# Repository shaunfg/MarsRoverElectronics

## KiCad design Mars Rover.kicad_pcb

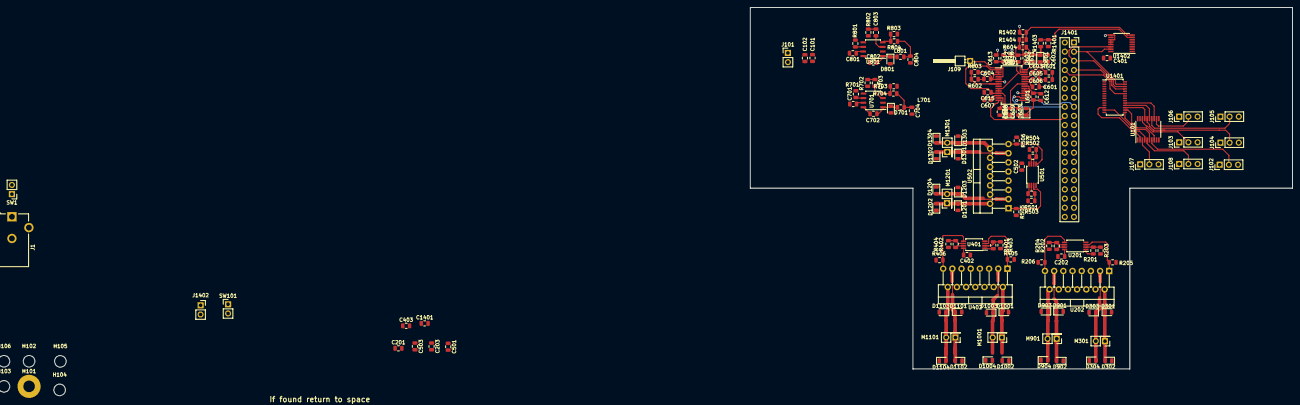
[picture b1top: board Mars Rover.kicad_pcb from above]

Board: 2 copper layers, 150.0 x 100.0 mm, 141 parts (0 on the bottom side), 101 nets.

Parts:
C101, C614, C616: 22uF; C_0805_2012Metric
C102, C601, C602, C605, C606, C610, C611, C612: 0.1uF; C_0805_2012Metric
C201, C202, C203, C401, C402, C403, C501, C502, C503: 100nF; C_0805_2012Metric
C603, C607, C608: 1nF; C_0805_2012Metric
C604: 1uF; C_0805_2012Metric
C609, C701, C702, C801, C802, C1401: C; C_0805_2012Metric
C613: 0.22uF; C_0805_2012Metric
C615: 4.7uF; C_0805_2012Metric
C703, C704, C803, C804: 220pF; C_0805_2012Metric
D301, D302, D303, D304, D601, D604, D901, D902, D903, D904, D1001, D1002, D1003, D1004, D1101, D1102, D1103, D1104, D1201, D1202, D1203, D1204, D1301, D1302, D1303, D1304: DIODE; D_0805_2012Metric
D602, D603, D701, D801: D_Schottky; D_0805_2012Metric
H101: MountingHole_Pad; MountingHole_3.2mm_M3_Pad
H102, H103, H104, H105, H106: MountingHole; MountingHole_3.2mm_M3
J1: Barrel_Jack; BarrelJack_CUI_PJ-102AH_Horizontal
J101: Conn_01x02; PinHeader_1x02_P2.54mm_Vertical
J102, J103, J104, J105, J106, J107, J108: Conn_01x03; PinHeader_1x03_P2.54mm_Vertical
J109: Conn_01x01; PinHeader_1x01_P2.54mm_Horizontal
J1401: Raspberry_Pi_2_3; PinSocket_2x20_P2.54mm_Vertical
J1402: Conn_01x02; PinSocket_1x02_P2.54mm_Vertical
L601: INDUCTOR; L_0805_2012Metric
L701, L801: L; L_0805_2012Metric
M301, M901, M1001, M1101, M1201, M1301: Motor_DC; PinHeader_2x01_P2.54mm_Vertical
R201, R202, R401, R402, R501, R502: 1k; R_0805_2012Metric
R203, R204, R403, R404, R503, R504, R601, R703, R803: 10k; R_0805_2012Metric
R205, R206, R405, R406, R505, R506: 200mR; R_0805_2012Metric
R602, R603, R1401, R1402, R1403, R1404: R; R_0805_2012Metric
R604: 0.05R; R_0805_2012Metric
R701, R801: 200k; R_0805_2012Metric
R702, R802: 68k; R_0805_2012Metric
R704: 51k; R_0805_2012Metric
R804: 75k; R_0805_2012Metric
SW1: KILLSWITCH; PinHeader_1x02_P2.54mm_Vertical
SW101: CHARGING; PinHeader_1x02_P2.54mm_Vertical
U101: 74HCT244; TSSOP-20_4.4x6.5mm_P0.65mm
U201, U401, U501: OP279; TSSOP-8_4.4x3mm_P0.65mm
U202, U402, U502: L298HN; TO-220-15_P2.54x2.54mm_StaggerOdd_Lead4.58mm_Vertical
U601: MAX1758; SSOP-28_5.3x10.2mm_P0.65mm
U701, U801: MP2467; SOIC-8_3.9x4.9mm_P1.27mm
U1401: PCA9685PW; TSSOP-28_4.4x9.7mm_P0.65mm
U1402: ADS7828; TSSOP-16_4.4x5mm_P0.65mm

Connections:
+3V3: J1401.1, J1401.17
+5V: C201.2, C202.1, C401.2, C402.1, C501.2, C502.1, C704.1, C1401.1, J1401.2, J1401.4, J1402.1, L701.2, R704.2, U201.8, U202.6, U202.9, U202.11, U401.8, U402.6, U402.9, U402.11, U501.8, U502.6, U502.9, U502.11, U1401.28, U1402.16
+7.5V: C804.1, J102.3, J103.3, J104.3, J105.3, J106.3, J107.3, J108.3, L801.2, R804.2, U101.20
+12V: C203.2, C403.2, C503.2, C801.1, D301.2, D303.2, D901.2, D903.2, D1001.2, D1003.2, D1101.2, D1103.2, D1201.2, D1203.2, D1301.2, D1303.2, SW101.2, U202.4, U402.4, U502.4, U801.7
/Battery Connection and Charge Management/BATT: C101.1, C102.2, J101.2, U601.8
/Battery Connection and Charge Management/CHRG_VL: C615.1, D604.1, U601.1, U601.11
/Battery Connection and Charge Management/THERM: J109.1, U601.4
/Battery Connection and Charge Management/~FASTCHRG: J1401.15, U601.15
/Battery Connection and Charge Management/~FAULT: J1401.18, U601.14
/Battery Connection and Charge Management/~FULLCHRG: J1401.16, U601.16
/Digital logic/HK0: R201.1, U201.1, U1402.1
/Digital logic/HK1: R202.1, U201.7, U1402.2
/Digital logic/HK2: R401.1, U401.1, U1402.3
/Digital logic/HK3: R402.1, U401.7, U1402.4
/Digital logic/HK4: R501.1, U501.1, U1402.5
/Digital logic/HK5: R502.1, U501.7, U1402.6
/Digital logic/POL0: J1401.35, U202.7
/Digital logic/POL1: J1401.38, U202.12
/Digital logic/POL2: J1401.40, U402.7
/Digital logic/POL3: J1401.36, U402.12
/Digital logic/POL4: J1401.27, U502.7
/Digital logic/POL5: J1401.28, U502.12
/Digital logic/PWM0: U202.5, U1401.6
/Digital logic/PWM1: U202.10, U1401.7
/Digital logic/PWM2: U402.5, U1401.8
/Digital logic/PWM3: U402.10, U1401.9
/Digital logic/PWM4: U502.5, U1401.10
/Digital logic/PWM5: U502.10, U1401.11
/Digital logic/PWM6: U101.2, U1401.12
/Digital logic/PWM7: U101.4, U1401.13
/Digital logic/PWM8: U101.6, U1401.15
/Digital logic/PWM9: U101.8, U1401.16
/Digital logic/PWMA: U101.17, U1401.17
/Digital logic/PWMB: U101.15, U1401.18
/Digital logic/PWMC: U101.13, U1401.19
/Digital logic/SCL: J1401.5, U1401.26, U1402.14
/Digital logic/SDA: J1401.3, U1401.27, U1402.15
/Digital logic/~OE: J1401.8, U1401.23
/Motor/V1: D301.1, D302.2, M301.1, U202.2
/Motor/V2: D303.1, D304.2, M301.2, U202.3
/VIN_RAW: D601.1, D602.2, R1403.1, SW1.2
/VMOTOR: C610.2, C613.1, C614.1, C616.1, C701.1, R604.2, R1404.2, SW101.1, U601.9, U601.10, U601.26, U701.7
/sheet5C45D717/V1: D901.1, D902.2, M901.1, U202.13
/sheet5C45D717/V2: D903.1, D904.2, M901.2, U202.14
/sheet5C45DA5C/V1: D1001.1, D1002.2, M1001.1, U402.2
/sheet5C45DA5C/V2: D1003.1, D1004.2, M1001.2, U402.3
/sheet5C45DEF9/V1: D1101.1, D1102.2, M1101.1, U402.13
/sheet5C45DEF9/V2: D1103.1, D1104.2, M1101.2, U402.14
/sheet5C45F77A/V1: D1201.1, D1202.2, M1201.1, U502.2
/sheet5C45F77A/V2: D1203.1, D1204.2, M1201.2, U502.3
/sheet5C45FA3C/V1: D1301.1, D1302.2, M1301.1, U502.13
/sheet5C45FA3C/V2: D1303.1, D1304.2, M1301.2, U502.14
GND: C101.2, C102.1, C201.1, C202.2, C203.1, C401.1, C402.2, C403.1, C501.1, C502.2, C503.1, C601.2, C602.1, C603.2, C604.1, C605.2, C606.2, C607.2, C608.2, C610.1, C611.1, C612.2, C613.2, C614.2, C615.2, C616.2, C701.2, C704.2, C801.2, C804.2, C1401.2, D302.1, D304.1, D603.2, D701.2, D801.2, D902.1, D904.1, D1002.1, D1004.1, D1102.1, D1104.1, D1202.1, D1204.1, D1302.1, D1304.1, H101.1, J1.2, J101.1, J102.1, J103.1, J104.1, J105.1, J106.1, J107.1, J108.1, J1401.6, J1401.9, J1401.14, J1401.20, J1401.25, J1401.30, J1401.34, J1401.39, J1402.2, R203.2, R204.2, R205.2, R206.2, R403.2, R404.2, R405.2, R406.2, R503.2, R504.2, R505.2, R506.2, R602.2, R701.1, R702.2, R703.1, R801.1, R802.2, R803.1, R1401.2, R1402.2, U101.1, U101.10, U101.19, U201.4, U202.8, U401.4, U402.8, U501.4, U502.8, U601.6, U601.18, U701.5, U801.5, U1401.1, U1401.2, U1401.3, U1401.4, U1401.5, U1401.14, U1401.24, U1402.9, U1402.11, U1402.12, U1402.13
unnamed: C601.1, R601.2
unnamed: C602.2, D601.2, U601.28
unnamed: C603.1, R601.1, U601.25
unnamed: C604.2, R603.2, U601.2, U601.3, U601.5
unnamed: C605.1, U601.24
unnamed: C606.1, U601.23
unnamed: C607.1, U601.12
unnamed: C608.1, U601.13
unnamed: C609.1, D603.1, L601.1, U601.19, U601.20
unnamed: C609.2, D604.2, U601.22
unnamed: C611.2, D602.1, R604.1, U601.27
unnamed: C612.1, L601.2, U601.21
unnamed: C702.1, U701.8
unnamed: C702.2, D701.1, L701.1, U701.1
unnamed: C703.1, U701.3
unnamed: C703.2, R702.1
unnamed: C802.1, U801.8
unnamed: C802.2, D801.1, L801.1, U801.1
unnamed: C803.1, U801.3
unnamed: C803.2, R802.1
unnamed: J1.1, SW1.1
unnamed: J102.2, U101.7
unnamed: J103.2, U101.18
unnamed: J104.2, U101.16
unnamed: J105.2, U101.14
unnamed: J106.2, U101.12
unnamed: J107.2, U101.3
unnamed: J108.2, U101.5
unnamed: J1401.7, U1401.25
unnamed: R201.2, R203.1, U201.2
unnamed: R202.2, R204.1, U201.6
unnamed: R205.1, U201.3, U202.1
unnamed: R206.1, U201.5, U202.15
unnamed: R401.2, R403.1, U401.2
unnamed: R402.2, R404.1, U401.6
unnamed: R405.1, U401.3, U402.1
unnamed: R406.1, U401.5, U402.15
unnamed: R501.2, R503.1, U501.2
unnamed: R502.2, R504.1, U501.6
unnamed: R505.1, U501.3, U502.1
unnamed: R506.1, U501.5, U502.15
unnamed: R602.1, R603.1, U601.7
unnamed: R701.2, U701.6
unnamed: R703.2, R704.1, U701.4
unnamed: R801.2, U801.6
unnamed: R803.2, R804.1, U801.4
unnamed: R1401.1, R1403.2, U1402.7
unnamed: R1402.1, R1404.1, U1402.8

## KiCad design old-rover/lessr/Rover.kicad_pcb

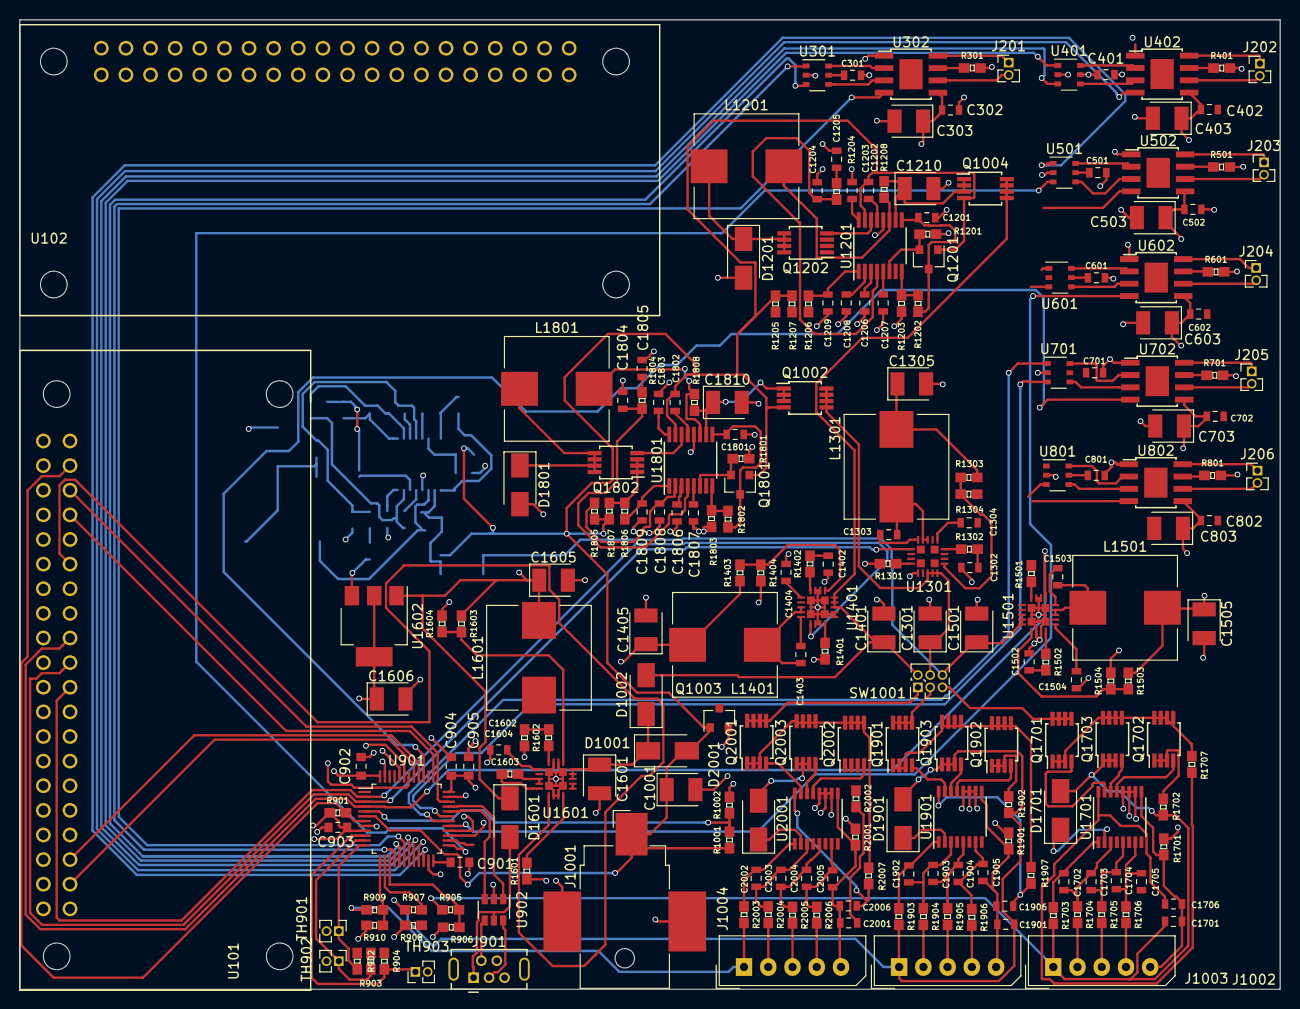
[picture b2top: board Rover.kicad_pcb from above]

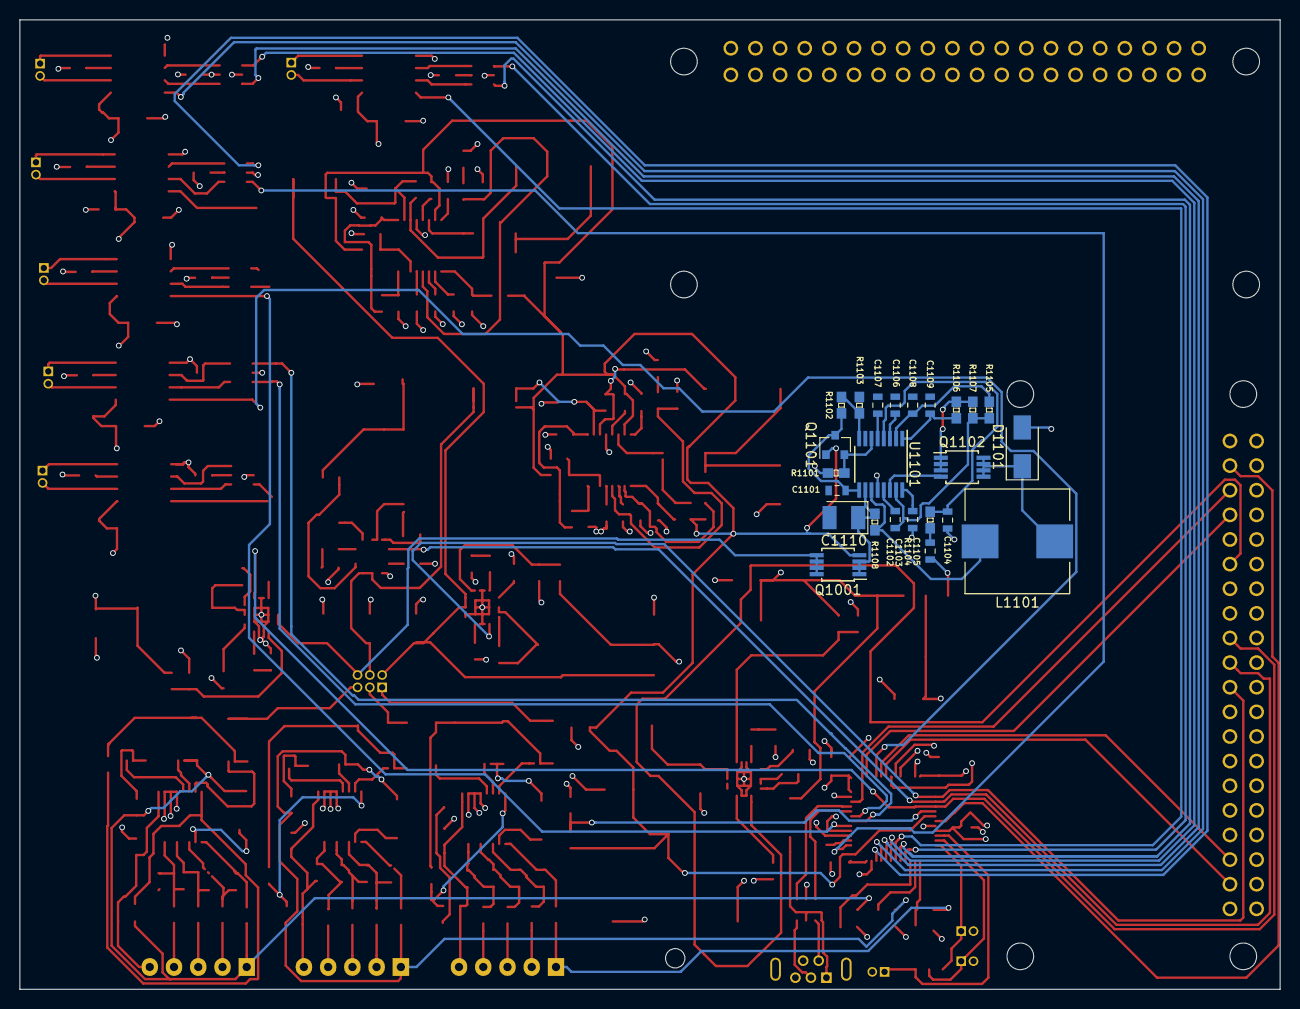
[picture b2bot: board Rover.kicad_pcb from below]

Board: 4 copper layers, 130.0 x 100.0 mm, 249 parts (24 on the bottom side), 208 nets.

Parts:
C301, C401, C501, C601, C701, C801, C1104, C1105, C1204, C1205, C1303, C1403, C1503, C1701, C1703, C1704, C1705, C1804, C1805, C1901, C1903, C1904, C1905, C2001, C2003, C2004, C2005: 100nF; C_0603_1608Metric
C302, C402, C502, C602, C702, C802: 10uF; C_0603_1608Metric
C303, C403, C503, C603, C703, C803, C1001, C1110, C1210, C1301, C1305, C1401, C1405, C1501, C1505, C1601, C1605, C1606, C1810: 22uF; CP_EIA-3528-21_Kemet-B
C901, C902, C903, C904: 100nF; C_0603_1608Metric_Pad0.84x1.00mm_HandSolder
C905: 1uF; C_0603_1608Metric_Pad0.84x1.00mm_HandSolder
C1101, C1201, C1702, C1801, C1902, C2002: 1uF; C_0603_1608Metric
C1102, C1202, C1802: 22nF; C_0603_1608Metric
C1103, C1203, C1706, C1803, C1906, C2006: 2.2uF; C_0603_1608Metric
C1106, C1107, C1206, C1207, C1806, C1807: 47nF; C_0603_1608Metric
C1108, C1109, C1208, C1209, C1302, C1304, C1402, C1404, C1502, C1504, C1604, C1808, C1809: 10nF; C_0603_1608Metric
C1602: 10nF; 0603
C1603: 100nF; 0603
D1001, D1002, D1101, D1201, D1601, D1701, D1801, D1901, D2001: B360; D_SMA
J201, J202, J203, J204, J205, J206: Conn_01x02; PinHeader_1x02_P1.27mm_Vertical
J901: USB_B_Micro; USB_Micro-B_Tensility_54-00023_Vertical
J1001: Jack-DC; BarrelJack_CUI_PJ-036AH-SMT_Horizontal
J1002, J1003, J1004: Conn_01x05; Molex_SPOX_5267-05A_1x05_P2.50mm_Vertical
L1101, L1201, L1301, L1401, L1501, L1601, L1801: 10uH; L_Wuerth_HCI-1030
Q1001, Q1002, Q1004, Q1102, Q1202, Q1701, Q1702, Q1703, Q1802, Q1901, Q1902, Q1903, Q2001, Q2002, Q2003: IRF7606PBF; MSOP-8_3x3mm_P0.65mm
Q1003, Q1101, Q1201, Q1801: 2N7002; SOT-23
R301, R401, R501, R601, R701, R801: 0.22R; 0603
R901, R1101, R1104, R1201, R1204, R1304, R1404, R1504, R1604, R1801, R1804: 10k; 0603
R902, R903, R904: 500R; 0603
R905, R907, R909: 120k; 0603
R906, R908, R910: 20k; 0603
R1001, R1102, R1103, R1202, R1203, R1802, R1803: 100k; 0603
R1002: 15k; 0603
R1105, R1106, R1205, R1206, R1805, R1806: 4R7; 0603
R1107, R1207, R1807: 0.033R; 0603
R1108, R1208, R1808: 0.068R; 0603
R1301, R1401, R1501, R1601: 29k; 0603
R1302, R1402, R1502, R1602: 1k7; 0603
R1303, R1403, R1503: 140k; 0603
R1603: 52k5; 0603
R1701, R1901, R2001: 0.02R; 0603
R1702, R1902, R2002: 510R; 0603
R1703, R1903, R2003: 51R; 0603
R1704, R1705, R1706, R1904, R1905, R1906, R2004, R2005, R2006: 1k; 0603
R1707, R1907, R2007: 10R; 0603
SW1001: SW_DIP_x03; PinHeader_2x03_P1.27mm_Vertical
TH901, TH902, TH903: KTY81; PinHeader_1x02_P1.27mm_Vertical
U101, U102: Rpi0w; raspi0w
U301, U401, U501, U601, U701, U801: 74LVC1G18GW; TSOP-6_1.65x3.05mm_P0.95mm
U302, U402, U502, U602, U702, U802: DRV8872-Q1; TI_SO-PowerPAD-8
U901: STM32F042C4Tx; LQFP-48_7x7mm_P0.5mm
U902: USBLC6; SOT-23-6
U1101, U1201, U1801: MAX1873TEEE; QSOP-16_3.9x4.9mm_P0.635mm
U1301, U1401, U1501, U1601: TPS54620; TPS54610
U1602: LM1117MPX-3.3/NOPB; SOT-223-3_TabPin2
U1701, U1901, U2001: MAX1894; SSOP-16_3.9x4.9mm_P0.635mm

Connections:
+3V3: R902.1, R903.1, R904.1
+12V: C302.1, C303.1, C402.1, C403.1, C502.1, C503.1, C602.1, C603.1, C702.1, C703.1, C802.1, C803.1, C1305.1, C1405.1, C1505.1, L1301.2, L1401.2, L1501.2, R1303.1, R1403.1, R1503.1, U302.5, U402.5, U502.5, U602.5, U702.5, U802.5
/CPU/3V3: C301.1, C401.1, C501.1, C601.1, C701.1, C801.1, C901.1, C902.1, C903.1, C904.1, C905.1, C1606.1, R901.1, U301.5, U401.5, U501.5, U601.5, U701.5, U801.5, U901.9, U901.24, U901.36, U901.48, U1602.2
/CPU/BANK1_GD: U101.23, U901.4, U1501.14
/CPU/BANK1_V: C2001.2, D2001.2, J1004.1, Q2003.1, Q2003.2, Q2003.3, R909.1, R2002.1, R2003.2
/CPU/BANK2_GD: U101.21, U901.3, U1301.14
/CPU/BANK2_V: C1901.2, D1901.2, J1003.1, Q1903.1, Q1903.2, Q1903.3, R907.1, R1902.1, R1903.2
/CPU/BANK3_GD: U101.19, U901.2, U1401.14
/CPU/BANK3_V: C1701.2, D1701.2, J1002.1, Q1703.1, Q1703.2, Q1703.3, R905.1, R1702.1, R1703.2
/CPU/CHARGE_OK: C1001.1, C1202.1, C1802.1, D1001.2, J1001.1, Q1001.4, Q1002.4, Q1003.1, Q1004.4, Q1101.1, Q1201.1, Q1801.1, R1001.1, R1205.1, R1207.2, R1805.1, R1807.2, U901.6, U1201.15, U1801.15
/CPU/DC_CONN: R1001.2, R1002.1, U901.5
/CPU/EXT_N: J901.2, U902.4
/CPU/EXT_P: J901.3, U902.6
/CPU/I2C_SCL: U101.5, U901.40
/CPU/I2C_SDA: U101.3, U901.41
/CPU/INT_N: U901.32, U902.3
/CPU/INT_P: U901.33, U902.1
/CPU/MOT0_POL: U301.1, U901.16
/CPU/MOT0_PWM: U301.3, U901.17
/CPU/MOT0_nFAULT: U302.4, U901.18
/CPU/MOT1_POL: U401.1, U901.19
/CPU/MOT1_PWM: U401.3, U901.20
/CPU/MOT1_nFAULT: U402.4, U901.21
/CPU/MOT2_POL: U501.1, U901.22
/CPU/MOT2_PWM: U501.3, U901.25
/CPU/MOT2_nFAULT: U502.4, U901.26
/CPU/MOT3_POL: U601.1, U901.27
/CPU/MOT3_PWM: U601.3, U901.28
/CPU/MOT3_nFAULT: U602.4, U901.29
/CPU/SWCLK: U101.33, U901.37
/CPU/SWDIO: U101.35, U901.34
/CPU/SWEEP_POL: U701.1, U901.30
/CPU/SWEEP_PWM: U701.3, U901.31
/CPU/SWEEP_nFAULT: U702.4, U901.39
/CPU/TRAY_POL: U801.1, U901.42
/CPU/TRAY_PWM: U801.3, U901.43
/CPU/TRAY_nFAULT: U802.4, U901.44
/CPU/V_USB: D1601.2, J901.1, U902.5
/CPU/nRST: R901.2, U101.37, U901.7
/motordrive/MOT0_DRV/MOTL: J201.1, U302.8
/motordrive/MOT0_DRV/MOTR: J201.2, U302.6
/motordrive/MOT1_DRV/MOTL: J202.1, U402.8
/motordrive/MOT1_DRV/MOTR: J202.2, U402.6
/motordrive/MOT2_DRV/MOTL: J203.1, U502.8
/motordrive/MOT2_DRV/MOTR: J203.2, U502.6
/motordrive/MOT3_DRV/MOTL: J204.1, U602.8
/motordrive/MOT3_DRV/MOTR: J204.2, U602.6
/motordrive/SWEEP_DRV/MOTL: J205.1, U702.8
/motordrive/SWEEP_DRV/MOTR: J205.2, U702.6
/motordrive/TRAY_DRV/MOTL: J206.1, U802.8
/motordrive/TRAY_DRV/MOTR: J206.2, U802.6
/power/5V: C1605.1, D1601.1, L1601.2, R1603.1, U101.2, U101.4, U102.2, U102.4, U1602.1
/power/BUCK_12V_BANK1/EN: Q1003.3, U1301.10, U1401.10, U1501.10
/power/BUCK_12V_BANK1/V_BATT: C1401.1, D1002.2, Q1004.5, Q1004.6, Q1004.7, Q1004.8, SW1001.2, U1401.4, U1401.5, U1401.6
/power/BUCK_12V_BANK2/V_BATT: C1301.1, Q1002.5, Q1002.6, Q1002.7, Q1002.8, SW1001.4, U1301.4, U1301.5, U1301.6
/power/BUCK_12V_BANK3/V_BATT: C1501.1, Q1001.5, Q1001.6, Q1001.7, Q1001.8, SW1001.6, U1501.4, U1501.5, U1501.6
/power/BUCK_DVCC/V_BATT: C1601.1, D1001.1, D1002.1, U1601.4, U1601.5, U1601.6
/power/CHARGE_BANK1/BATT_+VE: C1210.1, Q1004.1, Q1004.2, Q1004.3, R1208.1, U1201.10
/power/CHARGE_BANK2/BATT_+VE: C1810.1, Q1002.1, Q1002.2, Q1002.3, R1808.1, U1801.10
/power/CHARGE_BANK3/BATT_+VE: C1110.1, Q1001.1, Q1001.2, Q1001.3, R1108.1, U1101.10
/power/CHARGE_BANK3/DC_JACK_IN: C1102.1, R1105.1, R1107.2, U1101.15
/power/DIGI_GOOD: U101.29, U1601.14
/power/PROTECT_BANK1/CELL1N: C2001.1, C2005.1, C2006.1, J1004.5, R2001.2, U2001.9
/power/PROTECT_BANK1/CELL1P: J1004.4, R2006.2
/power/PROTECT_BANK1/CELL2P: J1004.3, R2005.2
/power/PROTECT_BANK1/CELL3P: J1004.2, R2004.2
/power/PROTECT_BANK1/PACKP: Q2001.5, Q2001.6, Q2001.7, Q2001.8, SW1001.1
/power/PROTECT_BANK2/CELL1N: C1901.1, C1905.1, C1906.1, J1003.5, R1901.2, U1901.9
/power/PROTECT_BANK2/CELL1P: J1003.4, R1906.2
/power/PROTECT_BANK2/CELL2P: J1003.3, R1905.2
/power/PROTECT_BANK2/CELL3P: J1003.2, R1904.2
/power/PROTECT_BANK2/PACKP: Q1901.5, Q1901.6, Q1901.7, Q1901.8, SW1001.3
/power/PROTECT_BANK3/CELL1N: C1701.1, C1705.1, C1706.1, J1002.5, R1701.2, U1701.9
/power/PROTECT_BANK3/CELL1P: J1002.4, R1706.2
/power/PROTECT_BANK3/CELL2P: J1002.3, R1705.2
/power/PROTECT_BANK3/CELL3P: J1002.2, R1704.2
/power/PROTECT_BANK3/PACKP: Q1701.5, Q1701.6, Q1701.7, Q1701.8, SW1001.5
GND: C301.2, C302.2, C303.2, C401.2, C402.2, C403.2, C501.2, C502.2, C503.2, C601.2, C602.2, C603.2, C701.2, C702.2, C703.2, C801.2, C802.2, C803.2, C901.2, C902.2, C903.2, C904.2, C905.2, C1001.2, C1101.1, C1103.1, C1104.1, C1105.1, C1106.1, C1107.1, C1108.1, C1109.1, C1110.2, C1201.1, C1203.1, C1204.1, C1205.1, C1206.1, C1207.1, C1208.1, C1209.1, C1210.2, C1301.2, C1302.1, C1304.1, C1305.2, C1401.2, C1402.1, C1404.1, C1405.2, C1501.2, C1502.1, C1504.1, C1505.2, C1601.2, C1602.1, C1604.1, C1605.2, C1606.2, C1801.1, C1803.1, C1804.1, C1805.1, C1806.1, C1807.1, C1808.1, C1809.1, C1810.2, D1101.2, D1201.2, D1801.2, J901.5, J901.6, J1001.2, J1001.3, Q1003.2, R301.2, R401.2, R501.2, R601.2, R701.2, R801.2, R906.2, R908.2, R910.2, R1002.2, R1101.2, R1103.2, R1201.2, R1203.2, R1301.1, R1304.2, R1401.1, R1404.2, R1501.1, R1504.2, R1601.1, R1604.2, R1701.1, R1801.2, R1803.2, R1901.1, R2001.1, TH901.2, TH902.2, TH903.2, U101.6, U101.9, U101.14, U101.20, U101.25, U101.34, U101.39, U102.6, U102.9, U102.14, U102.20, U102.25, U102.30, U102.34, U102.39, U301.2, U302.1, U401.2, U402.1, U501.2, U502.1, U601.2, U602.1, U701.2, U702.1, U801.2, U802.1, U901.8, U901.23, U901.35, U901.47, U902.2, U1101.12, U1201.12, U1301.2, U1301.3, U1301.15, U1401.2, U1401.3, U1401.15, U1501.2, U1501.3, U1501.15, U1601.2, U1601.3, U1601.15, U1602.3, U1701.10, U1701.11, U1701.12, U1801.12, U1901.10, U1901.11, U1901.12, U2001.10, U2001.11, U2001.12
unnamed: C1101.2, Q1101.3, R1102.1, U1101.9
unnamed: C1102.2, U1101.13
unnamed: C1103.2, U1101.16
unnamed: C1104.2, R1104.1, U1101.4
unnamed: C1105.2, R1104.2
unnamed: C1106.2, U1101.3
unnamed: C1107.2, U1101.5
unnamed: C1108.2, R1105.2, U1101.2
unnamed: C1109.2, R1106.2, U1101.1
unnamed: C1201.2, Q1201.3, R1202.1, U1201.9
unnamed: C1202.2, U1201.13
unnamed: C1203.2, U1201.16
unnamed: C1204.2, R1204.1, U1201.4
unnamed: C1205.2, R1204.2
unnamed: C1206.2, U1201.3
unnamed: C1207.2, U1201.5
unnamed: C1208.2, R1205.2, U1201.2
unnamed: C1209.2, R1206.2, U1201.1
unnamed: C1302.2, R1302.2
unnamed: C1303.1, L1301.1, U1301.11, U1301.12
unnamed: C1303.2, U1301.13
unnamed: C1304.2, U1301.9
unnamed: C1402.2, R1402.2
unnamed: C1403.1, L1401.1, U1401.11, U1401.12
unnamed: C1403.2, U1401.13
unnamed: C1404.2, U1401.9
unnamed: C1502.2, R1502.2
unnamed: C1503.1, L1501.1, U1501.11, U1501.12
unnamed: C1503.2, U1501.13
unnamed: C1504.2, U1501.9
unnamed: C1602.2, R1602.2
unnamed: C1603.1, L1601.1, U1601.11, U1601.12
unnamed: C1603.2, U1601.13
unnamed: C1604.2, U1601.9
unnamed: C1702.1, C1703.2, R1704.1, U1701.3
unnamed: C1702.2, R1703.1, U1701.1
unnamed: C1703.1, C1704.2, R1705.1, U1701.5
unnamed: C1704.1, C1705.2, R1706.1, U1701.7
unnamed: C1706.2, R1707.1, U1701.16
unnamed: C1801.2, Q1801.3, R1802.1, U1801.9
unnamed: C1802.2, U1801.13
unnamed: C1803.2, U1801.16
unnamed: C1804.2, R1804.1, U1801.4
unnamed: C1805.2, R1804.2
unnamed: C1806.2, U1801.3
unnamed: C1807.2, U1801.5
unnamed: C1808.2, R1805.2, U1801.2
unnamed: C1809.2, R1806.2, U1801.1
unnamed: C1902.1, C1903.2, R1904.1, U1901.3
unnamed: C1902.2, R1903.1, U1901.1
unnamed: C1903.1, C1904.2, R1905.1, U1901.5
unnamed: C1904.1, C1905.2, R1906.1, U1901.7
unnamed: C1906.2, R1907.1, U1901.16
unnamed: C2002.1, C2003.2, R2004.1, U2001.3
unnamed: C2002.2, R2003.1, U2001.1
unnamed: C2003.1, C2004.2, R2005.1, U2001.5
unnamed: C2004.1, C2005.2, R2006.1, U2001.7
unnamed: C2006.2, R2007.1, U2001.16
unnamed: D1101.1, L1101.1, Q1102.5, Q1102.6, Q1102.7, Q1102.8
unnamed: D1201.1, L1201.1, Q1202.5, Q1202.6, Q1202.7, Q1202.8
unnamed: D1701.1, U1701.2
unnamed: D1801.1, L1801.1, Q1802.5, Q1802.6, Q1802.7, Q1802.8
unnamed: D1901.1, U1901.2
unnamed: D2001.1, U2001.2
unnamed: L1101.2, R1108.2, U1101.11
unnamed: L1201.2, R1208.2, U1201.11
unnamed: L1801.2, R1808.2, U1801.11
unnamed: Q1101.2, R1101.1, U1101.6
unnamed: Q1102.1, Q1102.2, Q1102.3, R1106.1, R1107.1
unnamed: Q1102.4, U1101.14
unnamed: Q1201.2, R1201.1, U1201.6
unnamed: Q1202.1, Q1202.2, Q1202.3, R1206.1, R1207.1
unnamed: Q1202.4, U1201.14
unnamed: Q1701.1, Q1701.2, Q1701.3, Q1702.5, Q1702.6, Q1702.7, Q1702.8, Q1703.5, Q1703.6, Q1703.7, Q1703.8, R1707.2
unnamed: Q1701.4, U1701.15
unnamed: Q1702.1, Q1702.2, Q1702.3, R1702.2
unnamed: Q1702.4, U1701.13
unnamed: Q1703.4, U1701.14
unnamed: Q1801.2, R1801.1, U1801.6
unnamed: Q1802.1, Q1802.2, Q1802.3, R1806.1, R1807.1
unnamed: Q1802.4, U1801.14
unnamed: Q1901.1, Q1901.2, Q1901.3, Q1902.5, Q1902.6, Q1902.7, Q1902.8, Q1903.5, Q1903.6, Q1903.7, Q1903.8, R1907.2
unnamed: Q1901.4, U1901.15
unnamed: Q1902.1, Q1902.2, Q1902.3, R1902.2
unnamed: Q1902.4, U1901.13
unnamed: Q1903.4, U1901.14
unnamed: Q2001.1, Q2001.2, Q2001.3, Q2002.5, Q2002.6, Q2002.7, Q2002.8, Q2003.5, Q2003.6, Q2003.7, Q2003.8, R2007.2
unnamed: Q2001.4, U2001.15
unnamed: Q2002.1, Q2002.2, Q2002.3, R2002.2
unnamed: Q2002.4, U2001.13
unnamed: Q2003.4, U2001.14
unnamed: R301.1, U302.7
unnamed: R401.1, U402.7
unnamed: R501.1, U502.7
unnamed: R601.1, U602.7
unnamed: R701.1, U702.7
unnamed: R801.1, U802.7
unnamed: R902.2, TH901.1, U901.12
unnamed: R903.2, TH902.1, U901.11
unnamed: R904.2, TH903.1, U901.10
unnamed: R905.2, R906.1, U901.15
unnamed: R907.2, R908.1, U901.14
unnamed: R909.2, R910.1, U901.13
unnamed: R1102.2, R1103.1, U1101.8
unnamed: R1202.2, R1203.1, U1201.8
unnamed: R1301.2, U1301.1
unnamed: R1302.1, U1301.8
unnamed: R1303.2, R1304.1, U1301.7
unnamed: R1401.2, U1401.1
unnamed: R1402.1, U1401.8
unnamed: R1403.2, R1404.1, U1401.7
unnamed: R1501.2, U1501.1
unnamed: R1502.1, U1501.8
unnamed: R1503.2, R1504.1, U1501.7
unnamed: R1601.2, U1601.1
unnamed: R1602.1, U1601.8
unnamed: R1603.2, R1604.1, U1601.7
unnamed: R1802.2, R1803.1, U1801.8
unnamed: U301.4, U302.3
unnamed: U301.6, U302.2
unnamed: U401.4, U402.3
unnamed: U401.6, U402.2
unnamed: U501.4, U502.3
unnamed: U501.6, U502.2
unnamed: U601.4, U602.3
unnamed: U601.6, U602.2
unnamed: U701.4, U702.3
unnamed: U701.6, U702.2
unnamed: U801.4, U802.3
unnamed: U801.6, U802.2

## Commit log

2018-12-06 battery half done
2018-12-06 Testing Commit
2018-12-13 Battery Charger Done
2019-01-17 Batteries done and raspi added
2019-01-25 Added housekeeping ADC, schematics almost done
2019-01-31 Schematics Done. Now need to do footprints
2019-02-14 Schematics done, now assigning footprints to do PCB Next
2019-02-14 Assigning footprints
2019-02-14 on to pcbs
2019-02-21 PCB - MAX 1758
2019-02-21 More layout
2019-03-14 updated layout
2019-03-21 Fixed Courtyard violations and moved diodes away from motor screw terminals
